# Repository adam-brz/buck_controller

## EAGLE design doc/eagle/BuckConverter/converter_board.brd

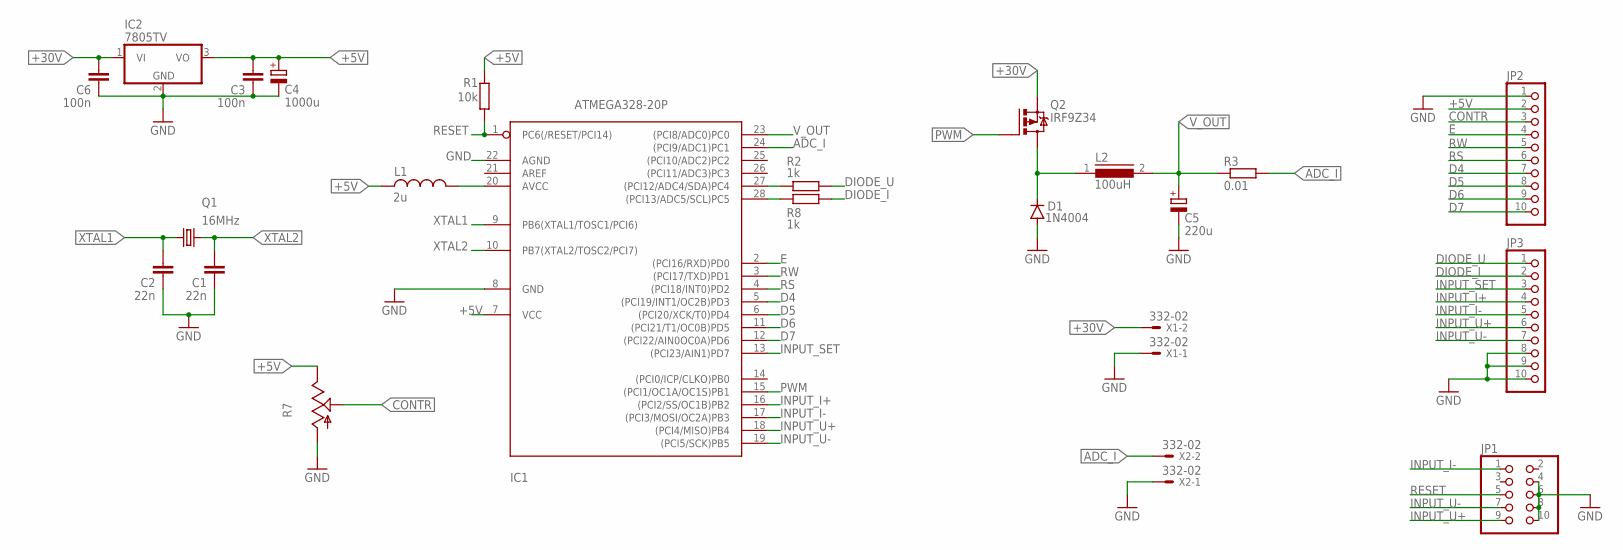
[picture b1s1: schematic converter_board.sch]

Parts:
C1, C2: 22n; C2.5-3
C3, C6: 100n; C2.5-3
C4: 1000u; E2,5-7
C5: 220u; E2,5-7
D1: 1N4004; DO41-10
IC1: ATMEGA328-20P; DIL28-3
IC2: 7805TV; TO220V
JP1: PINHD-2X5; 2X05
JP2, JP3: PINHD-1X10; 1X10
L1: 2u; 0204/7
L2: 100uH; ED26
Q1: 16MHz; HC49/S
Q2: IRF9Z34; TO220BH
R1: 10k; 0204/7
R2, R8: 1k; 0204/7
R3: 0.01; 0207/10
R7: TRIM_US-LI10; LI10
X1, X2: 332-02

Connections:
+5V: C3.2, C4.+, IC1.7 (VCC), IC2.3 (VO), JP2.2, L1.1, R1.2, R7.E
+30V: C6.2, IC2.1 (VI), Q2.S, X1.2
ADC_I: IC1.24 ((PCI9/ADC1)PC1), R3.2, X2.2
CONTR: JP2.3, R7.S
D4: IC1.5 ((PCI19/INT1/OC2B)PD3), JP2.7
D5: IC1.6 ((PCI20/XCK/T0)PD4), JP2.8
D6: IC1.11 ((PCI21/T1/OC0B)PD5), JP2.9
D7: IC1.12 ((PCI22/AIN0OC0A)PD6), JP2.10
DIODE_I: JP3.2, R8.1
DIODE_U: JP3.1, R2.1
E: IC1.2 ((PCI16/RXD)PD0), JP2.4
GND: C1.1, C2.1, C3.1, C4.-, C5.-, C6.1, D1.A, IC1.8 (GND), IC1.22 (AGND), IC2.2 (GND), JP1.4, JP1.6, JP1.8, JP1.10, JP2.1, JP3.8, JP3.9, JP3.10, R7.A, X1.1, X2.1
INPUT_I+: IC1.16 ((PCI2/SS/OC1B)PB2), JP3.4
INPUT_I-: IC1.17 ((PCI3/MOSI/OC2A)PB3), JP1.1, JP3.5
INPUT_SET: IC1.13 ((PCI23/AIN1)PD7), JP3.3
INPUT_U+: IC1.18 ((PCI4/MISO)PB4), JP1.9, JP3.6
INPUT_U-: IC1.19 ((PCI5/SCK)PB5), JP1.7, JP3.7
unnamed: IC1.20 (AVCC), L1.2
unnamed: D1.C, L2.1, Q2.D
unnamed: IC1.27 ((PCI12/ADC4/SDA)PC4), R2.2
unnamed: IC1.28 ((PCI13/ADC5/SCL)PC5), R8.2
PWM: IC1.15 ((PCI1/OC1A/OC1S)PB1), Q2.G
RESET: IC1.1 (PC6(/RESET/PCI14)), JP1.5, R1.1
RS: IC1.4 ((PCI18/INT0)PD2), JP2.6
RW: IC1.3 ((PCI17/TXD)PD1), JP2.5
V_OUT: C5.+, IC1.23 ((PCI8/ADC0)PC0), L2.2, R3.1
XTAL1: C2.2, IC1.9 (PB6(XTAL1/TOSC1/PCI6)), Q1.2
XTAL2: C1.2, IC1.10 (PB7(XTAL2/TOSC2/PCI7)), Q1.1

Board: 2 copper layers, 23 parts (0 on the bottom side), 28 nets, no tracks yet.

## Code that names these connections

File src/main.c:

/*
* buck_controller.c
*
* Created: 27.10.2021 23:52:03
* Author : Adam
*/

#include <stdbool.h>

#include <avr/io.h>
#include <util/delay.h>
#include <util/atomic.h>

#include "adc.h"
#include "buttons.h"
#include "controller.h"
#include "pwm_generator.h"
#include "timer.h"
#include "lcd_hd44780.h"
#include "fixed_point.h"

#define BUTTON_DELAY (200/1)
#define LCD_DELAY (500/2)

volatile uint8_t lcd_timer = 0;
volatile uint8_t btn_timer = 0;
volatile uint8_t measure_timer = 0;

int main(void)
{
	static FixedPoint U_set = 0;
	static FixedPoint I_set = 0;

	static FixedPoint U_measured = 0;
	static FixedPoint I_measured = 0;

	static uint16_t button_speed = 5;
	static bool blink = false;
	static bool voltage_changed = false;
	static bool current_changed = false;

	// Unused pins (configure as input with pull up)
	PORTB |= _BV(PB0);
	PORTC |= _BV(PC2) | _BV(PC3);

	// LEDs
	DDRC |= _BV(PC4) | _BV(PC5);
	PORTC |= _BV(PC4);

	// Buttons
	PORTD |= _BV(PD7);
	PORTB |= _BV(PB2) | _BV(PB3) | _BV(PB4) | _BV(PB5);

	// PWM signal output
	DDRB |= _BV(PB1);

	controller_timer0_init();
	pwm_timer1_init();
	timer2_init();

	lcd_init();
	adc_init();

	// Enable interrupts
	sei();

	while (1)
	{
		if(btn_I_plus_pressed())
		{
			if(btn_timer >= BUTTON_DELAY)
			{
				btn_timer = 0;
				current_changed = true;

				I_set += button_speed;

				if(I_set > 500)
					I_set = 500;

				button_speed += 1;
			}
		}
		else if (btn_I_minus_pressed())
		{
			if(btn_timer >= BUTTON_DELAY)
			{
				btn_timer = 0;
				current_changed = true;

				if(I_set < button_speed)
					I_set = 0;
				else
					I_set -= button_speed;

				button_speed += 1;
			}
		}
		else if (btn_U_plus_pressed())
		{
			if(btn_timer >= BUTTON_DELAY)
			{
				btn_timer = 0;
				voltage_changed = true;

				U_set += button_speed;

				if(U_set > 3000)
					U_set = 3000;

				button_speed += 1;
			}

		}
		else if (btn_U_minus_pressed())
		{
			if(btn_timer >= BUTTON_DELAY)
			{
				btn_timer = 0;
				voltage_changed = true;

				if(U_set < button_speed)
					U_set = 0;
				else
					U_set -= button_speed;

				button_speed += 1;
			}
		}
		else
		{
			button_speed = 5;
		}

		if(button_speed > 2000)
			button_speed = 2000;

		if (btn_SET_pressed() && btn_timer >= BUTTON_DELAY)
		{
			btn_timer = 0;

			voltage_changed = false;
			current_changed = false;

			controller_set_inputs(U_set, I_set);
		}

		if(measure_timer >= 1)
		{
			measure_timer = 0;
			U_measured = get_voltage();
			I_measured = get_current();
			controller_set_feedback(U_measured, I_measured);
		}

		if(lcd_timer >= LCD_DELAY)
		{
			lcd_timer = 0;
			blink = !blink;

			char voltage_info[16] = "U:              ";
			char current_info[16] = "I:              ";

			fixed_point_to_str(U_measured, &voltage_info[3]);

			if(!(blink && voltage_changed))
				fixed_point_to_str(U_set, &voltage_info[9]);

			fixed_point_to_str(I_measured, &current_info[3]);

			if(!(blink && current_changed))
				fixed_point_to_str(I_set, &current_info[9]);

			lcd_goto(0, 0);
			lcd_puttext(voltage_info);

			lcd_goto(0, 1);
			lcd_puttext(current_info);
		}
	}
}

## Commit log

2024-08-16 Initial commit: upload project files
